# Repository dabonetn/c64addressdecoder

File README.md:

# c64addressdecoder
Say hello to my first Kicad project... Time to wean myself off eagle.

Multiple Address Decoder replacement for U15 in C64

This is a D100, D200, D300, D500, D600 & D700 adapter board based on the schematics from Maciej Witkowiak @ https://github.com/ytmytm/c64-ciaide

Goes into a C64 longboard, replacing the 74LS138 at location U15.

These are ready for production at JLCPCB including the 3 surface mount parts. (2x74ls138s and a .1uf cap).

All you need for components are pinheaders for the motherboard socket, and then you can either solder on your wires to the output, or add header pins.

Thanks for Retro Tech Insanity (https://www.youtube.com/@retrotechinsanity3164) for the inspiration.

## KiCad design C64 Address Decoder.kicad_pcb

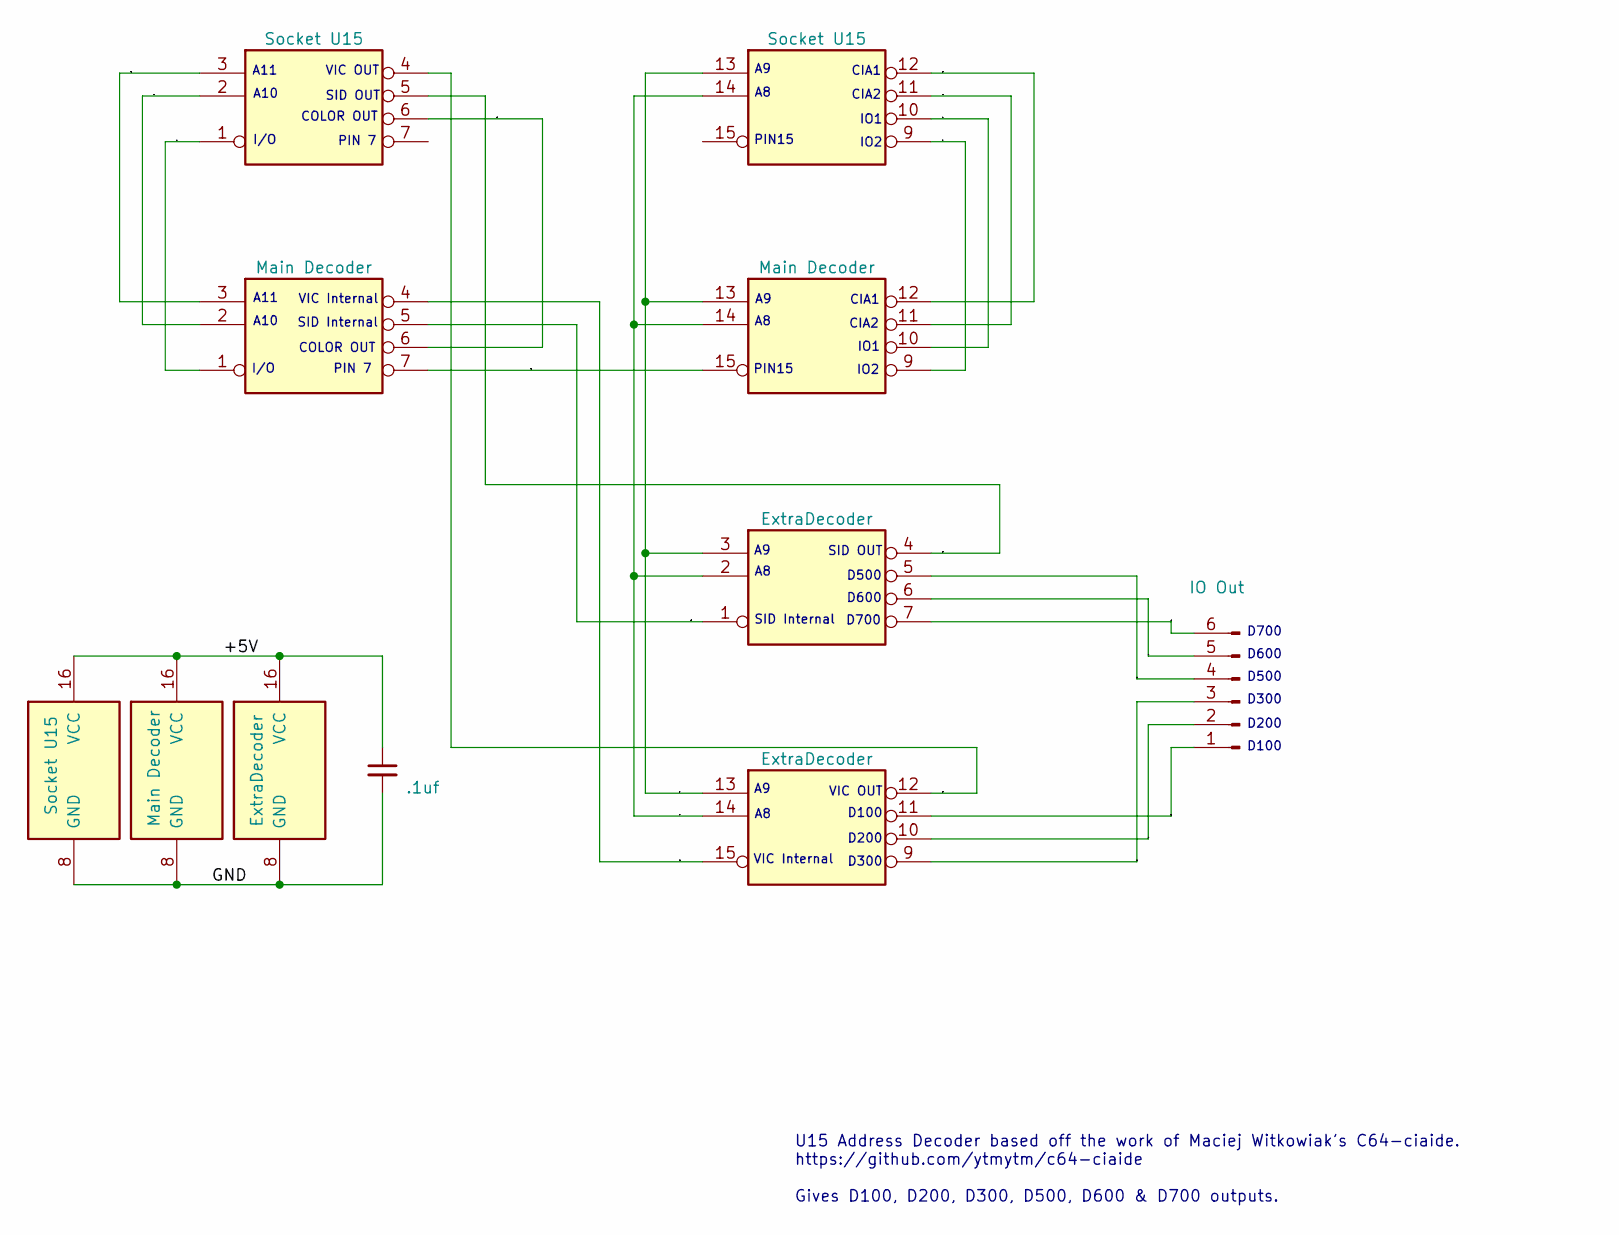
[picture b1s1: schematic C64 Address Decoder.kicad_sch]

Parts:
C1: .1uf; C_0805_2012Metric; LCSC C779984
J1: IO Out; PinHeader_1x06_P2.54mm_Vertical
U1: Socket U15; DIP-16_W7.62mm_LongPads
U2: Main Decoder; SOIC-16_4.55x10.3mm_P1.27mm; LCSC C521174
U3: ExtraDecoder; SOIC-16_4.55x10.3mm_P1.27mm; LCSC C521174

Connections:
/7TO15: U2.7 (O3), U2.15 (E)
/+5V: C1.1, U1.16 (VCC), U2.16 (VCC), U3.16 (VCC)
/A8: U1.14 (A0), U2.14 (A0), U3.2 (A0), U3.14 (A0)
/A9: U1.13 (A1), U2.13 (A1), U3.3 (A1), U3.13 (A1)
/A10: U1.2 (A0), U2.2 (A0)
/A11: U1.3 (A1), U2.3 (A1)
/CIA1: U1.12 (O0), U2.12 (O0)
/CIA2: U1.11 (O1), U2.11 (O1)
/COLOROUT: U1.6 (O2), U2.6 (O2)
/D100: J1.1, U3.11 (O1)
/D200: J1.2, U3.10 (O2)
/D300: J1.3, U3.9 (O3)
/D500: J1.4, U3.5 (O1)
/D600: J1.5, U3.6 (O2)
/D700: J1.6, U3.7 (O3)
/GND: C1.2, U1.8 (GND), U2.8 (GND), U3.8 (GND)
/IO1: U1.10 (O2), U2.10 (O2)
/IO2: U1.9 (O3), U2.9 (O3)
/I/O: U1.1 (E), U2.1 (E)
/SIDINT: U2.5 (O1), U3.1 (E)
/SIDOUT: U1.5 (O1), U3.4 (O0)
/VICINT: U2.4 (O0), U3.15 (E)
/VICOUT: U1.4 (O0), U3.12 (O0)

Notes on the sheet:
SID OUT
VIC Internal
PIN 7
VIC OUT
COLOR OUT
CIA2
IO1
I/O
D200
U15 Address Decoder based off the work of Maciej Witkowiak's C64-ciaide. https://github.com/ytmytm/c64-ciaide Gives D100, D200, D300, D500, D600 & D700 outputs.
D600
SID Internal
CIA1
D700
A10
IO2
PIN15
D100
A11
D500
D300

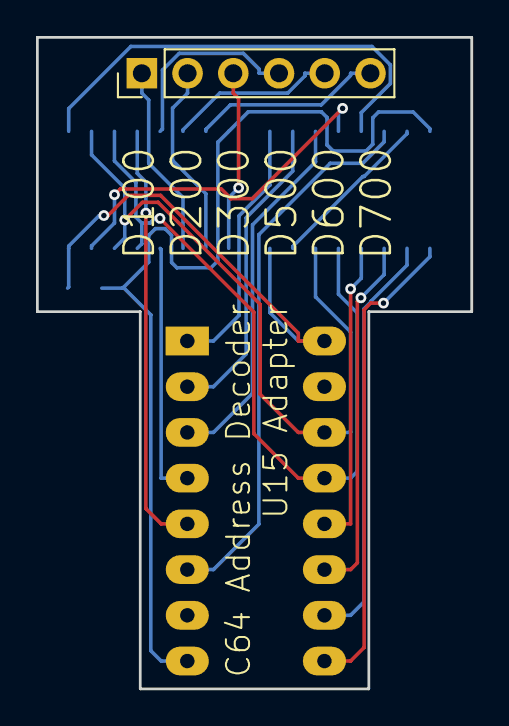
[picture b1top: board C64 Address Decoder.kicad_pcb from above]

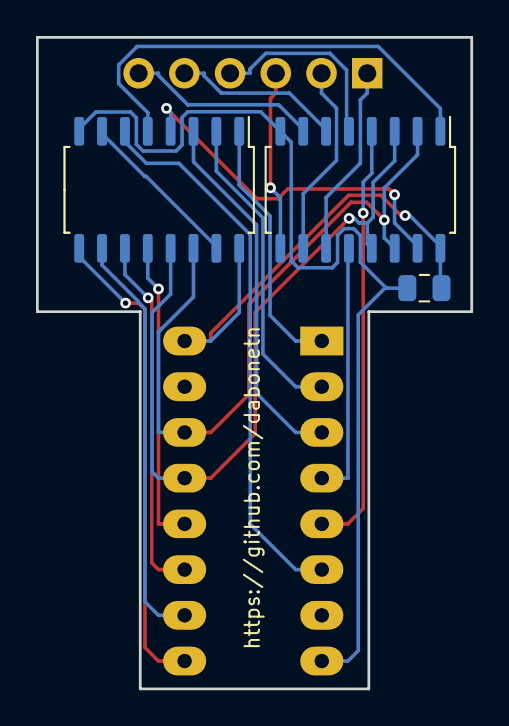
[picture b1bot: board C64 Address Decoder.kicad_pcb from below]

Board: 2 copper layers, 24.1 x 36.2 mm, 5 parts (3 on the bottom side), 23 nets.

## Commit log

2023-05-19 Initial Upload.
2023-06-09 Update README.md
    Boards are tested and working.
